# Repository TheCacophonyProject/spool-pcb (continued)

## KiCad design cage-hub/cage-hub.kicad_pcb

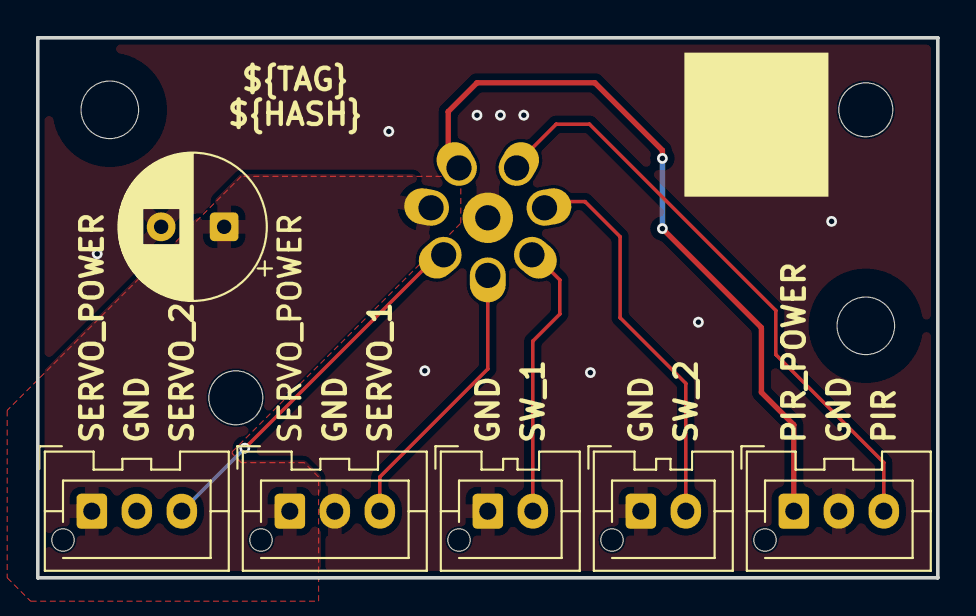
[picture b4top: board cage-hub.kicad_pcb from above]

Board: 2 copper layers, 50.0 x 30.0 mm, 12 parts (0 on the bottom side), 8 nets.

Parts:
C501: C_Polarized; CP_Radial_D8.0mm_P3.50mm
H202, H203: KeyHole; 3.0mm_key_hole
H403, H404: MountingHole; MountingHole_3.2mm_M3
J1, J5: Conn_01x02; JST_XA_B02B-XASK-1-A_1x02_P2.50mm_Vertical
J2, J3, J4: Conn_01x03; JST_XA_B03B-XASK-1-A_1x03_P2.50mm_Vertical
J205: JCON_M16_8Pin; jcon-8pin-m16
U1: JLCPCB_QR_8mm

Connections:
GND: C501.2, J1.1, J2.2, J3.2, J4.2, J5.1, J205.1
PIR_POWER: J4.1, J205.8
PIR_SIG: J4.3, J205.2
SERVO_POWER: C501.1, J2.1, J3.1, J205.7
SERVO_SIG_1: J2.3, J205.5
SERVO_SIG_2: J3.3, J205.6
SW_1: J1.2, J205.4
SW_2: J5.2, J205.3

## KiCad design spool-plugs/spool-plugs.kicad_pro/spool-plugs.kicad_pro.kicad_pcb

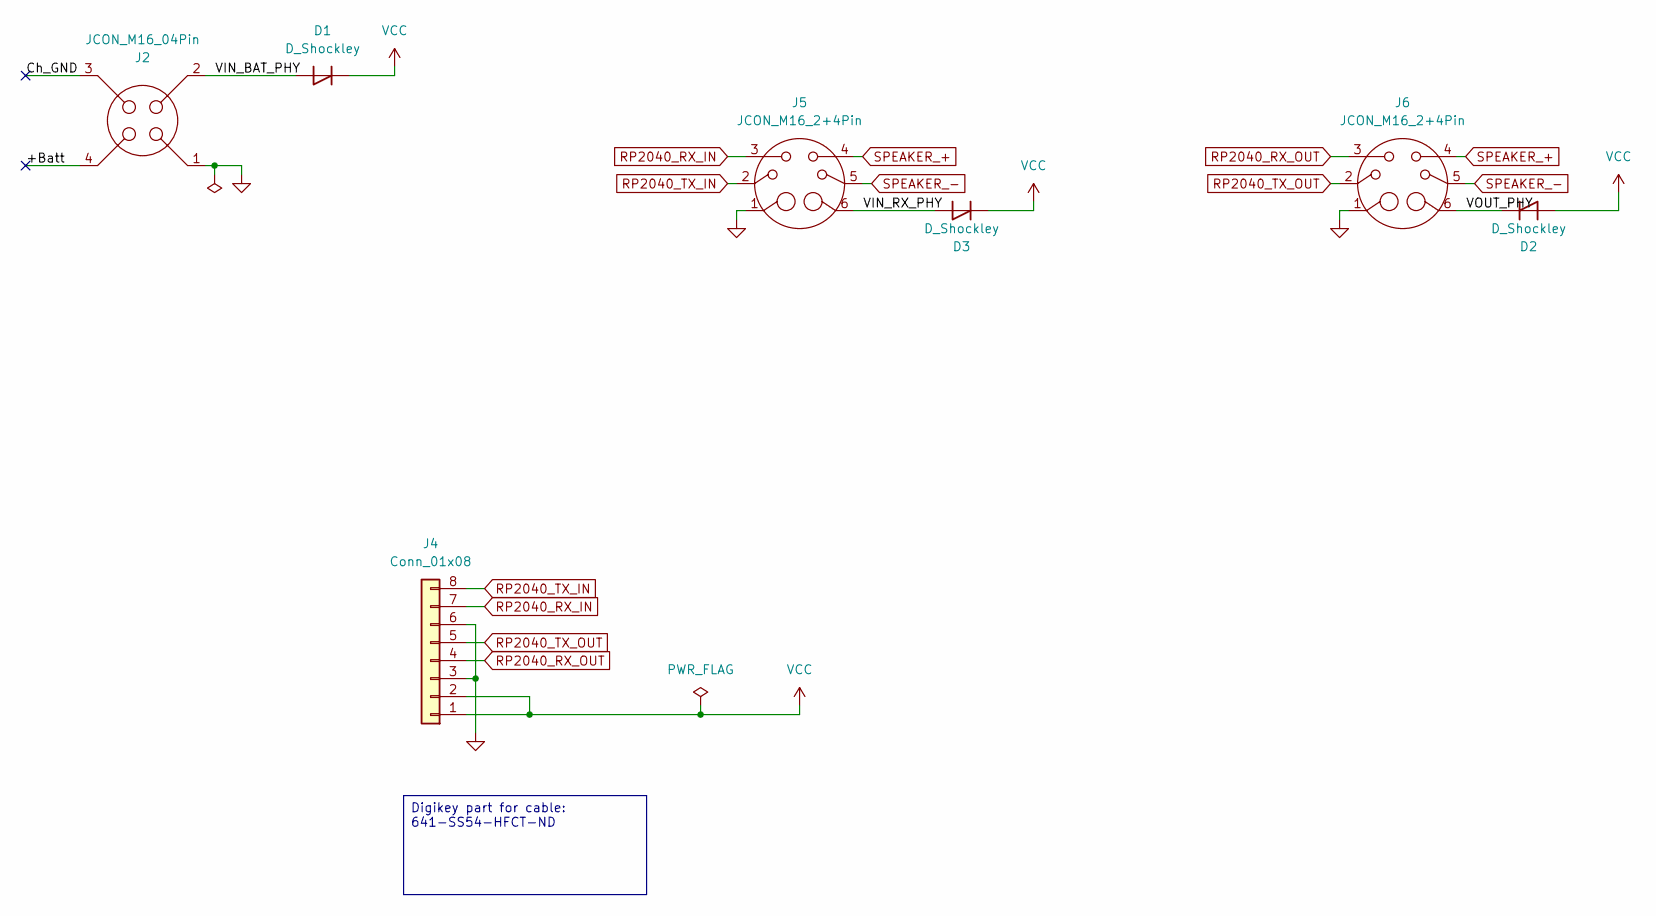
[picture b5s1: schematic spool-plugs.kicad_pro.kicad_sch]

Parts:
D1, D2, D3: D_Shockley; D_SMA_Handsoldering; LCSC C22452
J2: JCON_M16_04Pin; jcon-4pin_m16
J4: Conn_01x08; JST_XA_S08B-XASK-1_1x08_P2.50mm_Horizontal; Digikey 641-SS54-HFCT-ND
J5, J6: JCON_M16_2+4Pin; jcon-2+4pin-m16

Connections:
/+Batt: J2.4
/Ch_GND: J2.3
/VIN_BAT_PHY: D1.2 (A), J2.2
/VIN_RX_PHY: D3.2 (A), J5.6
/VOUT_PHY: D2.1 (K), J6.6
GND: J2.1, J4.3, J4.6, J5.1, J6.1
RP2040_RX_IN: J4.7, J5.3
RP2040_RX_OUT: J4.4, J6.3
RP2040_TX_IN: J4.8, J5.2
RP2040_TX_OUT: J4.5, J6.2
SPEAKER_+: J5.4, J6.4
SPEAKER_-: J5.5, J6.5
VCC: D1.1 (K), D2.2 (A), D3.1 (K), J4.1, J4.2

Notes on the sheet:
Digikey part for cable: 641-SS54-HFCT-ND

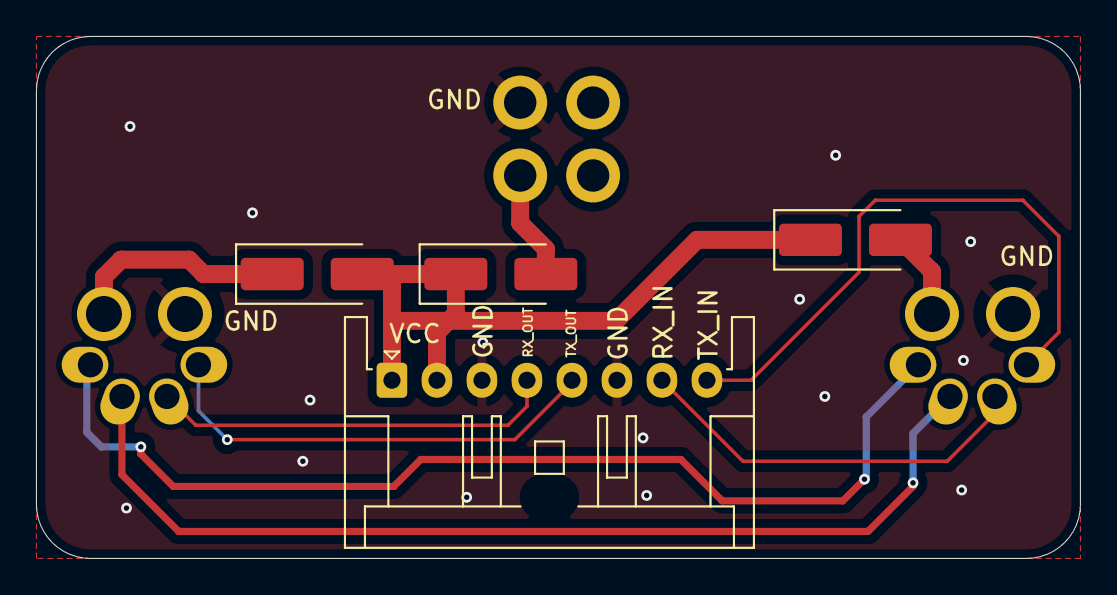
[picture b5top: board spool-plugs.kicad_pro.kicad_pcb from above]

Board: 4 copper layers, 58.0 x 29.0 mm, 7 parts (0 on the bottom side), 11 nets.

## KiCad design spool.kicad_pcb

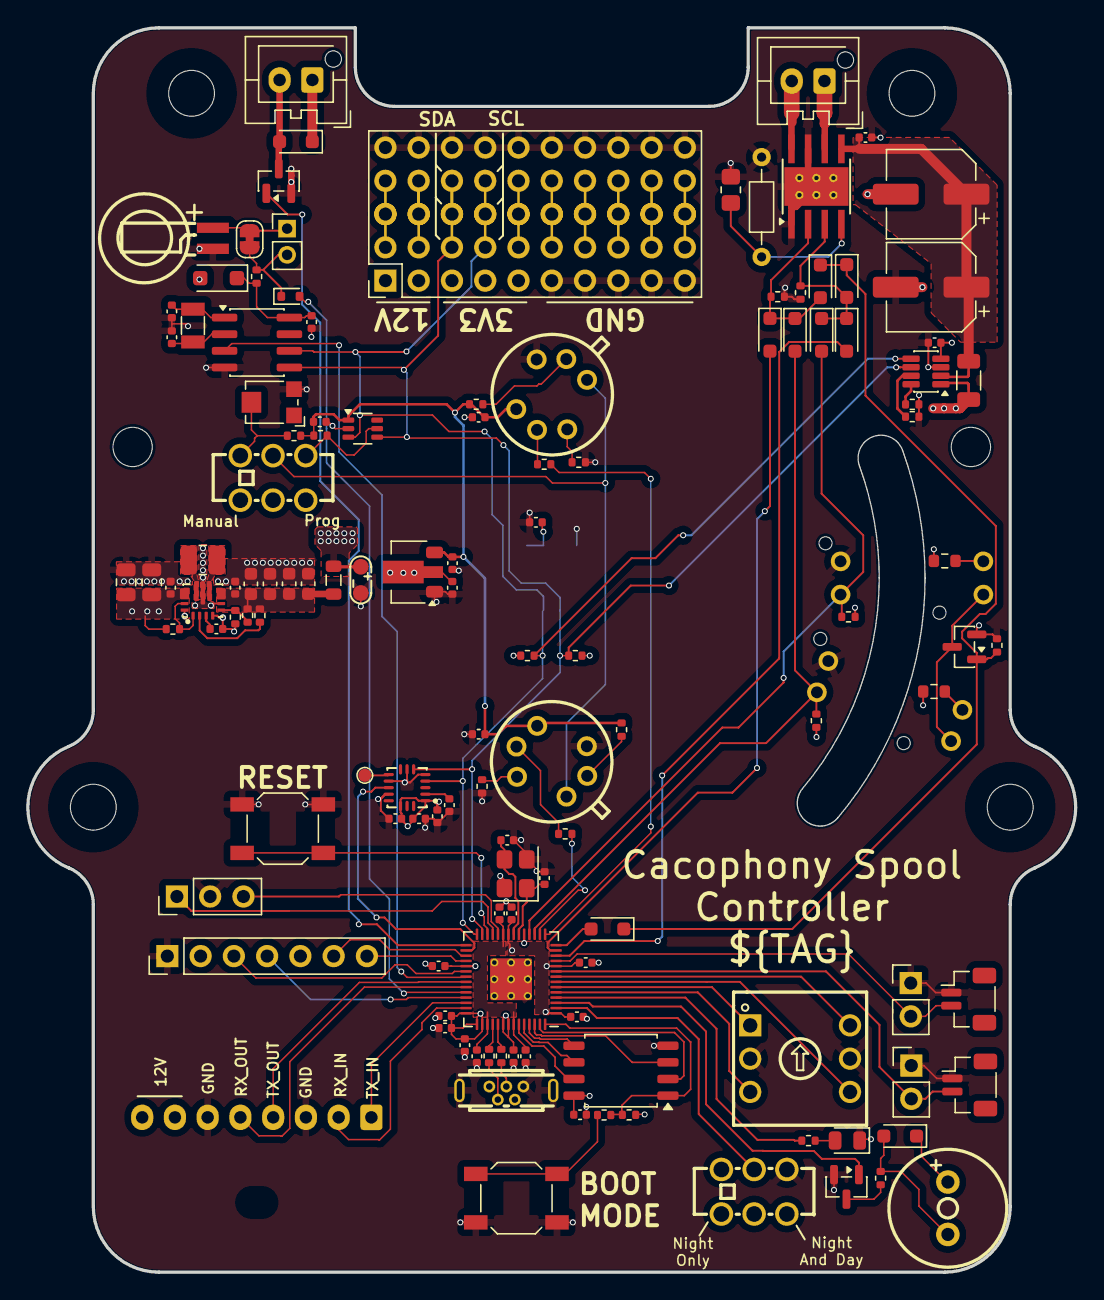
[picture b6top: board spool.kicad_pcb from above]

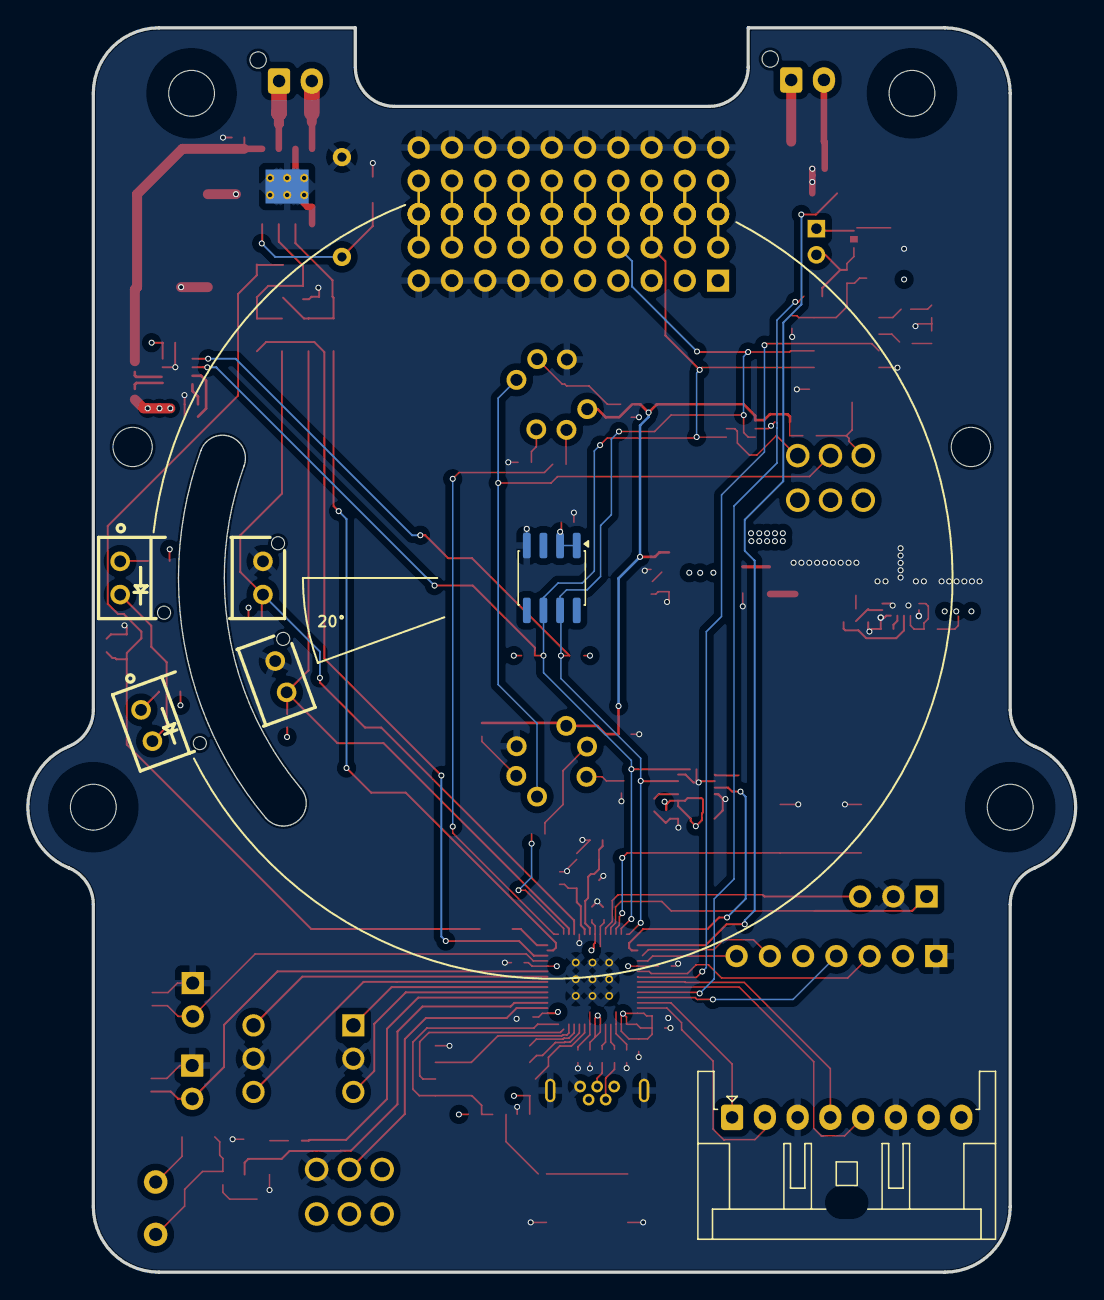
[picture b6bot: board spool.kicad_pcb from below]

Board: 4 copper layers, 80.0 x 95.0 mm, 135 parts (4 on the bottom side), 92 nets.

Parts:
BT1: Battery_Cell; CAP-SMD_FL11E
BZ1: Buzzer; BUZ-TH_BD9.0-P4.00-D0.6-FD
C1, C2: 22uF; C_0805_2012Metric
C3, C103, C105: 2.2uF; C_0402_1005Metric
C4, C10: 10uF; C_0402_1005Metric
C5, C6, C7, C8: 22uF; C_0603_1608Metric
C9: 100nF; C_0402_1005Metric
C11, C12, C13, C14, C15, C16, C17, C18, C19, C22, C27, C28, C29, C33, C101, C102, C104: 100n; C_0402_1005Metric
C20, C21, C25, C26, C30: 1uF; C_0402_1005Metric
C23, C24: 12pF; C_0402_1005Metric
C31, C32: 22pF; C_0402_1005Metric
C34, C35: 100uF; CP_Elec_6.3x7.7
D1: LED; LED_0805_2012Metric
D2: D; D_SOD-123F
D3: D; D_SOD-523
D4, D5, D6, D7, D8, D9, D10, D11, D101: D; D_SOD-323_HandSoldering
FB1: FerriteBead; L_0805_2012Metric
H1, H2, H3, H4: MountingHole; MountingHole_3.5mm_M3
H5, H6: MountingHole; 3.0mm_key_hole
J1: USB_B_Micro; MICRO-USB-TH_MICRO-USB-A14
J2: SWD; PinHeader_1x03_P2.54mm_Vertical
J3, J5: Switch_1; PinHeader_1x02_P2.54mm_Vertical
J4: Switch_1; JST_SH_BM02B-SRSS-TB_1x02-1MP_P1.00mm_Vertical
J6: Switch_2; JST_SH_BM02B-SRSS-TB_1x02-1MP_P1.00mm_Vertical
J7: Conn_01x02; PinHeader_1x02_P2.00mm_Vertical
J8: Conn_01x08; JST_XA_S08B-XASK-1_1x08_P2.50mm_Horizontal
J13: Conn_02x10_Counter_Clockwise; test-headers
J14: Conn_01x07; PinHeader_1x07_P2.54mm_Vertical
JP1: SolderJumper_2_Bridged; SolderJumper-2_P1.3mm_Bridged_RoundedPad1.0x1.5mm
L1: 1.5H; L_1008_2520Metric
L101: ElectromagneticActor; JST_XA_B02B-XASK-1-A_1x02_P2.50mm_Vertical
M1: Motor_DC; JST_XA_B02B-XASK-1-A_1x02_P2.50mm_Vertical
Q1: AO3400A; SOT-23
Q2: 2N7002; SOT-23
Q101: Q_NMOS_GSD; SOT-23
R1: 470k; R_0402_1005Metric
R2, R6, R7, R20, R21, R22, R23, R25, R27, R28, R29: 10k; R_0402_1005Metric
R3: 150k; R_0402_1005Metric
R4, R10, R12, R14, R101, R102: 100k; R_0402_1005Metric
R15: 47k; R_Axial_DIN0204_L3.6mm_D1.6mm_P7.62mm_Horizontal
R16, R17: 33ohm; R_0402_1005Metric
R18: DNF; R_0402_1005Metric
R19, R24, R26, R30, R32: 1k; R_0402_1005Metric
R31: 100R; R_0402_1005Metric
R33: 33k; R_0805_2012Metric_Pad1.20x1.40mm_HandSolder
R103: R_Shunt; R_1206_Shunt
R104, R105: 150Ω; R_0603_1608Metric
RV1: 10k; Potentiometer_Bourns_TC33X_Vertical
SW1: USB_BOOT; SW_SPST_SKQG_WithStem
SW2: RESET; SW_SPST_SKQG_WithStem
SW3, SW5: SW_Push_DPDT; SW-TH_K3-2235D-F1
SW4: SW_Coded_SH-7010; SW-TH_6P-L10.0-W10.0-P2.54-LS7.6_TSR-10
TP1: TestPoint_2Pole; test-point-2p
TP101: TestPoint; TP_PAD
U1: TPS63070RNMR; TPS63070
U3: AS5600-ASOT; SOIC-8_3.9x4.9mm_P1.27mm
U6: DRV8871DDA; Texas_HTSOP-8-1EP_3.9x4.9mm_P1.27mm_EP2.95x4.9mm_Mask2.4x3.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
U7: W25Q128JVS; SOIC-8_5.3x5.3mm_P1.27mm
U8: RP2040; RP2040-QFN-56
U9, U12: BS612; SENSORM-TH_BS612
U10: HT75xx-1-SOT89; SOT-89-3
U11: TPL0401B-10-Q1; Texas_R-PDSO-G6
U14: PCF8563T; SOIC-8_3.9x4.9mm_P1.27mm
U101: MMA8451QR1; QFN-16_L3.0-W3.0-P0.50-TL_FXOS8700CQR1
U102: INA219AxDCN; SOT-23-8
U103, U104: DY-ITR8402; OPTO-TH_DY-ITR8402
Y1: Crystal_GND24; Crystal_SMD_3225-4Pin_3.2x2.5mm
Y2: Crystal; Crystal_SMD_3215-2Pin_3.2x1.5mm

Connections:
+1V1: C11.1, C12.1, C20.1, U8.23 (DVDD), U8.45 (VREG_VOUT), U8.50 (DVDD)
+3V3: BZ1.1 (+), C10.1, C13.1, C14.1, C15.1, C16.1, C17.1, C18.1, C19.1, C21.1, C22.1, C101.1, C103.1, C104.1, C105.1, D2.2 (A), D11.1 (K), FB1.2, J13.5, J13.7, J13.9, J14.2, R6.1, R7.1, R18.1, R20.1, R21.1, R104.1, R105.1, TP1.2, U3.1 (VDD5V), U3.2 (VDD3V3), U7.8 (VCC), U8.1 (IOVDD), U8.10 (IOVDD), U8.22 (IOVDD), U8.33 (IOVDD), U8.42 (IOVDD), U8.43 (ADC_AVDD), U8.44 (VREG_IN), U8.48 (USB_VDD), U8.49 (IOVDD), U101.1 (VDDIO), U101.14 (VDD), U102.4 (VS)
+3V3_Lin: C26.1, C27.1, C28.1, C29.1, R22.1, R23.2, R27.2, R28.1, U9.4 (VDD), U10.3 (VOUT), U11.1 (VDD), U12.4 (VDD)
+12V: C1.1, C2.1, C3.1, C25.1, D101.1 (K), J8.7, J8.8, J13.1, J13.3, L101.1 (-), R2.1, R103.4, U1.12,13 (Vin), U10.2 (VIN)
/3V3_L1: L1.1, U1.11 (L1)
/3V3_L2: L1.2, U1.9 (L2)
/3V3_PHY: C4.1, C5.1, C6.1, C7.1, C8.1, FB1.1, R1.1, R4.1, U1.7,8 (Vout)
/PHOTO_1_ANODE: R104.2, U104.1
/PHOTO_2_ANODE: R105.2, U103.1
/PIR_SENS_POT_MANUAL: R23.1, RV1.2, SW3.1 (A)
/PIR_SENS_POT_PROG: R27.1, SW3.3 (C), U11.5 (W)
/QSPI_SCLK: U7.6 (CLK), U8.52 (QSPI_SCLK)
/QSPI_SD0: U7.5 (DI/IO_{0}), U8.53 (QSPI_SD0)
/QSPI_SD1: U7.2 (DO/IO_{1}), U8.55 (QSPI_SD1)
/QSPI_SD2: U7.3 (~WP/IO_{2}), U8.54 (QSPI_SD2)
/QSPI_SD3: U7.7 (~HOLD/~RESET/IO_{3}), U8.51 (QSPI_SD3)
/QSPI_SS: R18.2, R19.1, U7.1 (~CS), U8.56 (QSPI_SS)
/RTC_BAT: D3.1 (K), J7.2, JP1.2 (B), R32.2
/RTC_V_{DD}: C30.1, D2.1 (K), R32.1, U14.8 (VDD)
/RUN: SW2.2, U8.26 (RUN)
/SWCLK: J2.3, U8.24 (SWCLK)
/SWD: J2.1, U8.25 (SWD)
/USB_BOOT: R19.2, SW1.2
/USB_D+: J1.3 (D+), R16.2
/USB_D-: J1.2 (D-), R17.2
/USB_PHY_D+: R16.1, U8.47 (USB_DP)
/USB_PHY_D-: R17.1, U8.46 (USB_DM)
/h_bridge_vcc: C33.1, C34.1, C35.1, R103.1, U6.5 (VM)
Accel INT1: U8.30 (GPIO19), U101.11 (INT1)
BUZZER: Q2.1 (G), U8.3 (GPIO1)
EN_PHOTO: D4.1 (K), D5.1 (K), D6.1 (K), Q1.1 (G), R14.1
GND: BT1.2 (-), C1.2, C2.2, C3.2, C4.2, C5.2, C6.2, C7.2, C8.2, C9.2, C10.2, C11.2, C12.2, C13.2, C14.2, C15.2, C16.2, C17.2, C18.2, C19.2, C20.2, C21.2, C22.2, C23.1, C24.1, C25.2, C26.2, C27.2, C28.2, C29.2, C30.2, C31.2, C32.2, C33.2, C34.2, C35.2, C101.2, C102.2, C103.2, C104.2, C105.2, D1.1 (K), J1.5 (GND), J1.6 (Shield), J2.2, J3.1, J4.1, J5.1, J6.1, J8.3, J8.6, J13.11, J13.13, J13.15, J13.17, J13.19, J14.1, Q1.2 (S), Q2.2 (S), Q101.2 (S), R3.2, R10.2, R12.2, R14.2, R15.2, R25.1, R29.1, R33.2, R101.2, R102.2, RV1.3, SW1.1, SW2.1, SW4.C, SW5.3 (C), TP1.1, U1.4 (GND), U1.6 (FB2), U1.10 (PGND), U1.15 (Vsel), U3.4 (GND), U6.1 (GND), U6.7 (GND), U6.9 (GND), U7.4 (GND), U8.19 (TESTEN), U8.57 (GND), U9.3 (VSS), U10.1 (GND), U11.2 (GND), U12.3 (VSS), U14.4 (VSS), U101.5 (GND), U101.7 (SA0), U101.10 (GND), U101.12 (GND), U102.3 (GND), U103.4, U104.4, Y1.2 (G), Y1.4 (G)
GPIO_20: J14.6, U8.31 (GPIO20)
GPIO_21: J14.7, U8.32 (GPIO21)
GPIO_27: J14.4, U8.39 (GPIO27_ADC1)
GPIO_34: J14.3, U8.34 (GPIO22)
H_IN1: D9.2 (A), U8.12 (GPIO9)
H_IN2: D8.2 (A), U8.13 (GPIO10)
LED_1_PHY: R30.2, U8.4 (GPIO2)
NIGHT_ONLY: SW5.2 (B), U8.2 (GPIO0)
unnamed: BT1.1 (+), J7.1, JP1.1 (A)
unnamed: BZ1.2 (-), D11.2 (A), R31.1
unnamed: D1.2 (A), R30.1
unnamed: D4.2 (A), D7.1 (K), D8.1 (K), R12.1, U6.2 (IN2)
unnamed: D6.2 (A), U8.14 (GPIO11)
unnamed: D5.2 (A), D9.1 (K), D10.1 (K), R10.1, U6.3 (IN1)
unnamed: D101.2 (A), L101.2 (+), Q101.3 (D)
unnamed: M1.1 (+), U6.6 (OUT1)
unnamed: M1.2 (-), U6.8 (OUT2)
unnamed: Q2.3 (D), R31.2
unnamed: R2.2, U1.1 (PS/SYNC), U1.14 (EN)
unnamed: R1.2, R3.1, U1.5 (FB)
unnamed: R4.2, U1.2 (PG)
unnamed: C9.1, U1.3 (Vaux)
unnamed: R15.1, R33.1, U6.4 (ILIM)
unnamed: C23.2, U8.20 (XIN), Y1.1
unnamed: C24.2, U8.21 (XOUT), Y1.3
unnamed: R22.2, U9.2 (OEN)
unnamed: R25.2, U9.6 (ONTIME)
unnamed: R26.2, U9.5 (REL)
unnamed: R28.2, U12.2 (OEN)
unnamed: R29.2, U12.6 (ONTIME)
unnamed: R24.2, U12.5 (REL)
unnamed: C31.1, U14.1 (OSCI), Y2.2
unnamed: C32.1, U14.2 (OSCO), Y2.1
unnamed: C102.1, U101.2 (BYP)
unnamed: TP101.1, U101.9 (INT2)
unnamed: R101.1, U102.7 (A0)
unnamed: R102.1, U102.8 (A1)
unnamed: R103.3, U102.1 (IN+)
unnamed: R103.2, U102.2 (IN-)
PHOTO_CATHODE: Q1.3 (D), U103.2, U104.2
PHOTO_HOME_OUT: D10.2 (A), R6.2, U8.18 (GPIO15), U104.3
PHOTO_RESET_OUT: D7.2 (A), R7.2, U8.17 (GPIO14), U103.3
PIR_1: R26.1, U8.16 (GPIO13)
PIR_2: R24.1, U8.15 (GPIO12)
PIR_SENS_POT: SW3.2 (B), U9.1 (SENS), U12.1 (SENS)
RELEASE: Q101.1 (G), U8.29 (GPIO18)
RP2040_RX_IN: J8.2, U8.41 (GPIO29_ADC3)
RP2040_RX_OUT: J8.5, U8.37 (GPIO25)
RP2040_TX_IN: J8.1, U8.40 (GPIO28_ADC2)
RP2040_TX_OUT: J8.4, U8.36 (GPIO24)
RTC_BAT_SENSE: D3.2 (A), U8.38 (GPIO26_ADC0)
R_ENC_1: SW4.1, U8.6 (GPIO4)
R_ENC_2: SW4.2, U8.7 (GPIO5)
R_ENC_4: SW4.4, U8.5 (GPIO3)
R_ENC_8: SW4.8, U8.8 (GPIO6)
SCL: J13.8, R20.2, U3.7 (SCL), U8.28 (GPIO17), U11.3 (SCL), U14.6 (SCL), U101.4 (SCL), U102.5 (SCL)
SDA: J13.6, R21.2, U3.6 (SDA), U8.27 (GPIO16), U11.4 (SDA), U14.5 (SDA), U101.6 (SDA), U102.6 (SDA)
SWITCH_1: J3.2, J4.2, U8.9 (GPIO7)
SWITCH_2: J5.2, J6.2, U8.11 (GPIO8)
~RTC_INT: U8.35 (GPIO23), U14.3 (~INT)

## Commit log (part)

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2026-02-09 Add changes for magnet release
2026-02-09 Move files
2026-02-09 Added spool plugs
2026-02-10 Tidy up
2026-02-10 Add Readme file
2026-02-23 Add license
2026-06-03 Added solder helper
2026-06-03 Added PIR
2026-06-20 Add servo, more inputs and update board layout
2026-06-25 Update to use new PIR and added servo outputs
2026-06-26 Added kicad-library as submodule and simplify schematic
2026-06-26 Update kicad-library
2026-06-26 Update library paths
2026-06-26 Remove parts from position file
